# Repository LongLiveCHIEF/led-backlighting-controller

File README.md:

# LED Backlighting Controller

This project is designed to control a strip of ws2812 LED's that serve to backlight wall-hung art.

At the moment, in it's earliest viable release form, it has one momentary push button that is used
to cycle through the available solid color lighting choices.

Future updates for this project will support a potentiometer for dimming, and various animation modes.

## Build and Flash

```
cargo build --release
cargo hf2 --release
```

## Video Demo

## Electrical Schematic

## Power Usage
Power values below from ws2812 strip of 20 led's

| Color | mA @ max brightness | mA @ 50% brightness | mA @ 10% brightness |
| ----- | ------------------- | ------------------- | ------------------- |
| WHITE | 14.30 | 7.26 | 2.05 |
| RED | 5.28 | 3.13 | 1.74 |
| GREEN | 3.11 | 2.25 | 1.65 |
| BLUE | 5.26 | 3.15 | 1.73 |

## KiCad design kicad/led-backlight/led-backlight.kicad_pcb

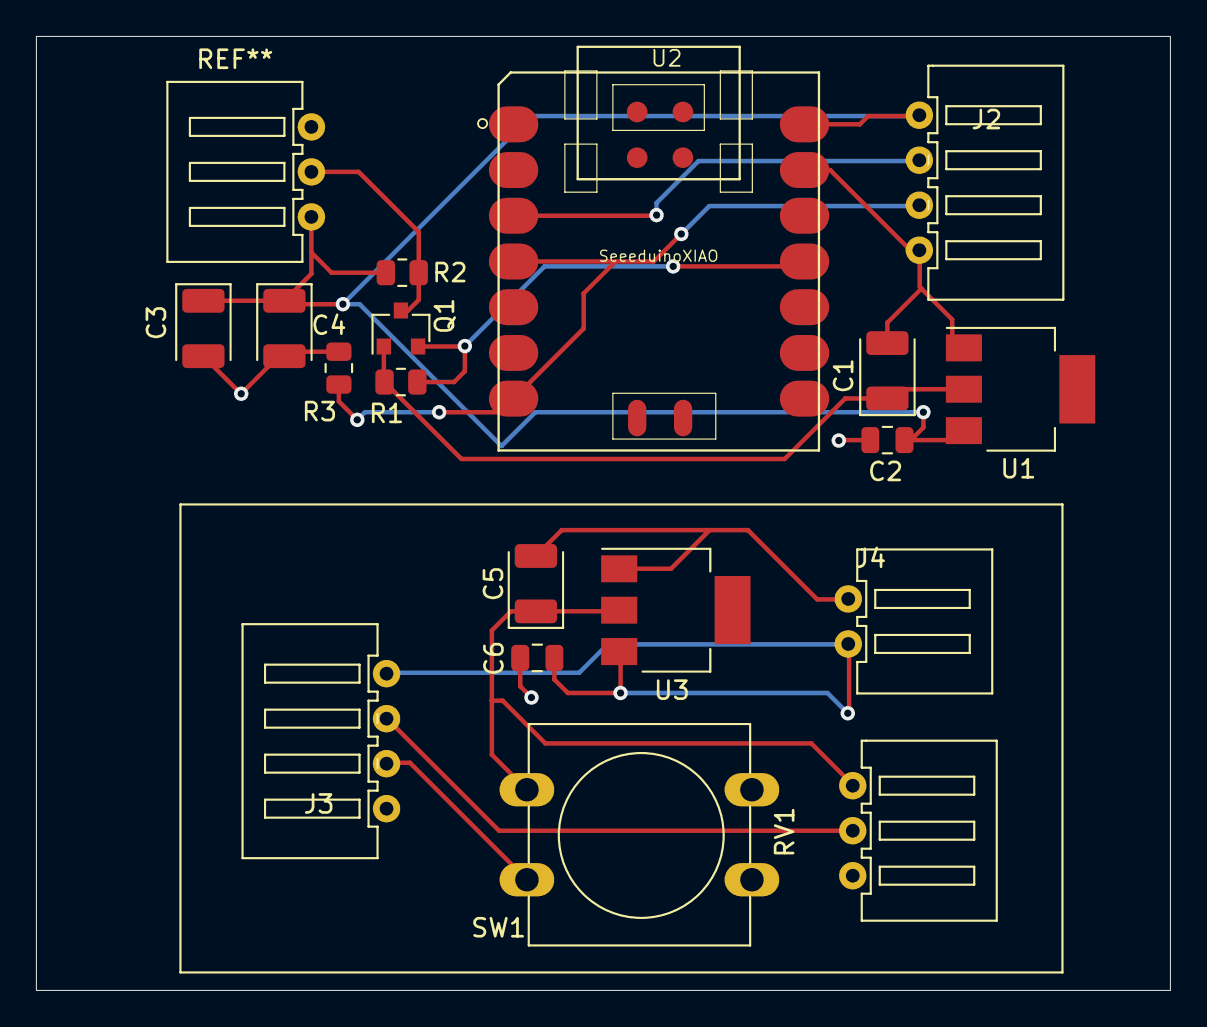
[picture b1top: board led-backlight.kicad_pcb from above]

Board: 2 copper layers, 63.0 x 53.0 mm, 18 parts (0 on the bottom side), 7 nets.

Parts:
C1, C5: 22uF; CP_EIA-3528-12_Kemet-T
C2, C6: 10uF; C_0805_2012Metric
C3, C4: 330uF; CP_EIA-3528-12_Kemet-T
J2, J3: jst_xh_conn_1x04_horizontal
J4: jst_xh_conn_1x02_horizontal
Q1: BSS138; SOT-23
R1, R2: 10k; R_0805_2012Metric
R3: R_0805_2012Metric
RV1: R_POT_US; jst_xh_conn_1x03_horizontal
SW1: SW_MEC_5E; SW_PUSH-12mm
U1, U3: AMS1117-3.3; SOT-223-3_TabPin2
U2: SeeeduinoXIAO; Seeeduino XIAO-MOUDLE14P-2.54-21X17.8MM

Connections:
+5V: C2.2, C3.1, C4.1, C6.2, J2.1, J3.1, R2.1, U1.3, U2.14, U3.3
/mcu_board/+3V: C1.1, Q1.1, R1.1, U1.2
/mcu_board/DataHigh: Q1.3, R2.2
/mcu_board/DataLow: Q1.2, R1.2, U2.11
/mcu_board/mode_btn: C5.1, J2.3, J3.2, R3.2, RV1.3, SW1.1, SW1.2, U2.4, U2.7, U3.2
/mcu_board/mode_ref: J2.2, J3.3, RV1.2, U2.3
GND: C1.2, C2.1, C3.2, C4.2, C5.2, C6.1, J3.4, J4.2, R3.1, RV1.1, U1.1, U2.13, U3.1

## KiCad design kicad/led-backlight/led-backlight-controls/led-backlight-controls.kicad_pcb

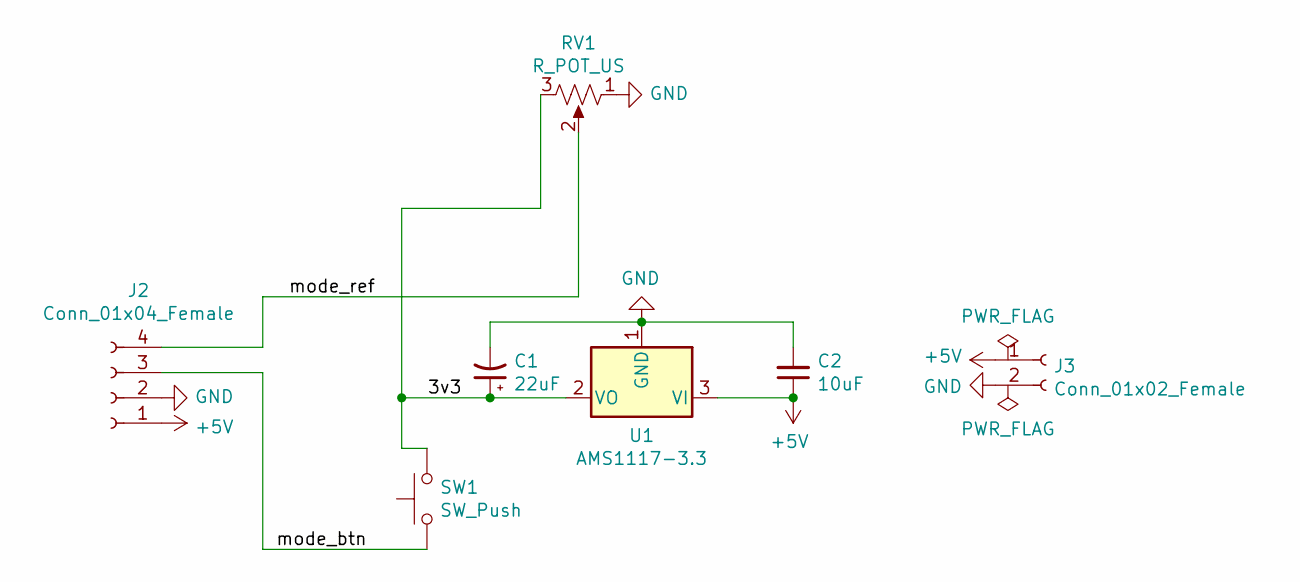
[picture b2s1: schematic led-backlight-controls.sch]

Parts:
C1: 22uF; CP_EIA-3528-12_Kemet-T
C2: 10uF; C_0805_2012Metric
J2: Conn_01x04_Female; jst_xh_conn_1x04_horizontal
J3: Conn_01x02_Female; jst_xh_conn_1x02_horizontal
RV1: R_POT_US; jst_xh_conn_1x03_horizontal
SW1: SW_Push; SW_PUSH-12mm
U1: AMS1117-3.3; SOT-223-3_TabPin2

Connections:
+5V: C2.1, J2.1, J3.1, U1.3 (VI)
/3v3: C1.1, RV1.3, SW1.2, U1.2 (VO)
/mode_btn: J2.3, SW1.1
/mode_ref: J2.4, RV1.2
GND: C1.2, C2.2, J2.2, J3.2, RV1.1, U1.1 (GND)

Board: 2 copper layers, 7 parts (0 on the bottom side), 5 nets, no tracks yet.

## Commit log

2021-04-09 setup a blinky pin
2021-04-09 prevent wfi sleep
2021-04-10 spawn blink task from init
2021-04-10 blinky
2021-04-23 use xiao_m0 bsc
2021-04-23 update probe speed
2021-04-24 for some reason using atsamd21e17 works on a g18
2021-04-24 update default probe
2021-04-24 update cargo config
2021-04-29 got serial to work i think
2021-05-02 add rainbow example
2021-05-03 add rgb-blinky.rs
2021-05-03 enable mosi_idle_high feature
2021-05-03 make a rainbow blinky with rtic!
2021-05-03 changed example names
2021-05-03 ensure optimizations so timing of spi
2021-05-04 disabled blinky in main, getting serious now
2021-05-04 prevent blindness during development
2021-05-05 cleanup notes
2021-05-06 patch ws2812-spi-rs
2021-05-06 correct NUM_LEDS value
2021-05-07 use more appropriate interrupt vector
2021-05-07 example buttons
2021-05-07 setup button as interrupt
2021-05-08 working hardware interrupt button
2021-05-08 tweak brightness
2021-05-09 add panic-rtt-target
2021-05-09 update linker config
2021-05-11 add onButtonInterrupt task
2021-05-11 add modeDetectPin
2021-05-11 configure pin 4 as mode detection pin
2021-05-12 create input-pin example
2021-05-12 add duration based debouncer
2021-05-13 remove unused code from examples
2021-05-13 tweak spi timing
2021-05-13 created writer function
2021-05-13 remove explicit color functions
2021-05-15 change log text
2021-05-23 make one led iterable
2021-05-23 resolve compiler warnings
2021-06-05 write to all leds on color change
2021-06-05 remove uneeded mut's
2021-06-05 add schematic
2021-06-06 added README
2021-06-06 add video demo to README
2021-06-06 add power documentation
2021-06-12 added new schematic
2021-06-13 set up control potentiometer
2021-06-13 log raw adc input
2021-06-13 no need for mut's
2021-06-13 fix controlKnob pin initialization
2021-06-13 brightness mapping during write
2021-06-13 undo
2021-07-17 finish kicad project v1
2021-07-17 add kicad project
2021-07-17 add ignores for kicad source control
2021-07-17 example
2021-07-17 schematics complete
2021-07-17 add board stackup
2021-07-17 update board track routing
2021-07-17 add pulldown resistor to eic pin
2021-09-03 idk can't remember
2021-09-03 add yellow, increase NUM_LEDS
2021-09-04 update NUM_LEDS to 35
2021-09-04 task documentation
2021-09-04 broken attempt at upgradeing rtic
2021-09-04 local static mut hold resource updated
2021-09-04 unexpectedly compiles
2021-09-04 change NUM_LEDS back to test num of 20
